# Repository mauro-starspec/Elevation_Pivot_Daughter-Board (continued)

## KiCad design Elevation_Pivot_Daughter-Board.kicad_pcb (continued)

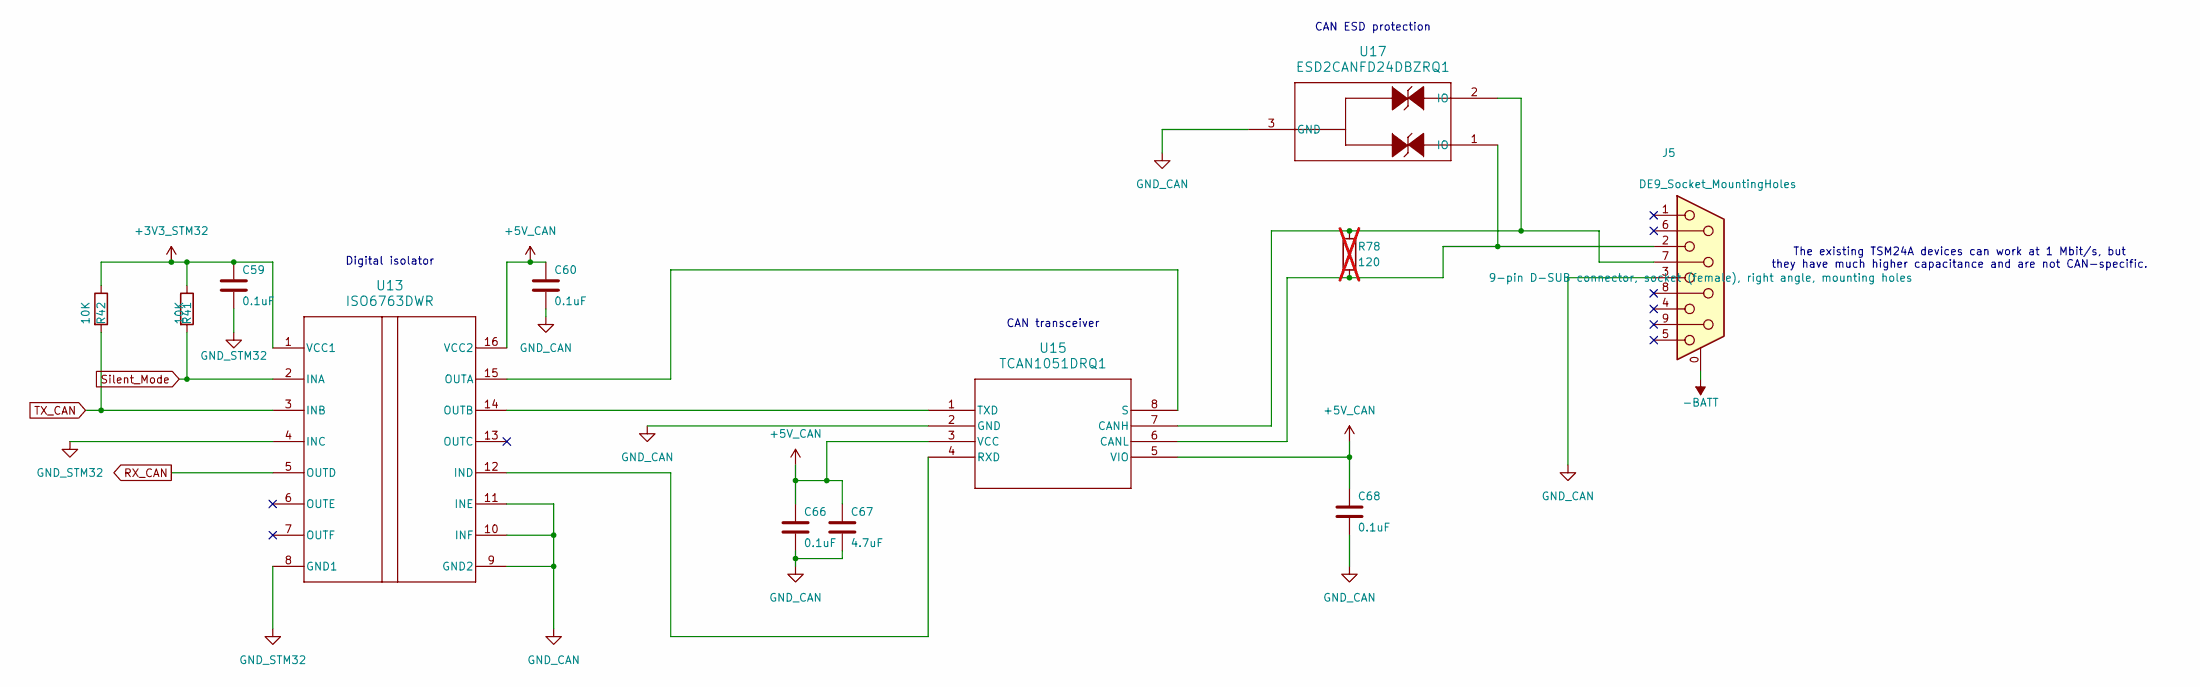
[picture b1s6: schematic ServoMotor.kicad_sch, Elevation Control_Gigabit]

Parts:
C59, C60, C66, C68: 0.1uF; C_0805_2012Metric; MANUFACTURER_PART_NUMBER CL21B104KCFNNNE; LCSC C28233
C67: 4.7uF; C_1210_3225Metric; MANUFACTURER_PART_NUMBER CL32B475KCVZNWE; LCSC C17288249
J5: DE9_Socket_MountingHoles; DSUB-9_Socket_Horizontal_P2.77x2.84mm_EdgePinOffset7.70mm_H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; MANUFACTURER_PART_NUMBER 5747844-4; LCSC C305941
R41, R42: 10K; R_0805_2012Metric; MANUFACTURER_PART_NUMBER RC0805FR-0710KL; LCSC C84376
R78: 120; R_0805_2012Metric_Pad1.20x1.40mm_HandSolder; MANUFACTURER_PART_NUMBER RC0805FR-07120RL; LCSC C114245; not fitted
U13: ISO6763DWR; MANUFACTURER_PART_NUMBER ISO6763DWR; LCSC C5216409
U15: TCAN1051DRQ1; TCAN1051HGVDRQ1; MANUFACTURER_PART_NUMBER TCAN1051DRQ1; LCSC C2671229
U17: ESD2CANFD24DBZRQ1; MANUFACTURER_PART_NUMBER ESD2CANFD24DBZRQ1; LCSC C20345392

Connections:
+3V3_STM32: C59.1, R41.1, R42.1, U13.1 (VCC1); also elsewhere on the board
+5V_CAN: C60.1, C66.1, C67.1, C68.1, U13.16 (VCC2), U15.3 (VCC), U15.5 (VIO); also elsewhere on the board
-BATT: J5.0 (PAD); also elsewhere on the board
GND_CAN: C60.2, C66.2, C67.2, C68.2, J5.3, U13.9 (GND2), U13.10 (INF), U13.11 (INE), U15.2 (GND), U17.3 (GND); also elsewhere on the board
GND_STM32: C59.2, U13.4 (INC), U13.8 (GND1); also elsewhere on the board
unnamed: U13.12 (IND), U15.4 (RXD)
unnamed: U13.15 (OUTA), U15.8 (S)
unnamed: U13.14 (OUTB), U15.1 (TXD)
unnamed: J5.7, R78.1, U15.7 (CANH), U17.2 (IO)
unnamed: J5.2, R78.2, U15.6 (CANL), U17.1 (IO)
RX_CAN: U13.5 (OUTD); also elsewhere on the board
Silent_Mode: R41.2, U13.2 (INA); also elsewhere on the board
TX_CAN: R42.2, U13.3 (INB); also elsewhere on the board

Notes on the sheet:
CAN ESD protection
Digital isolator
The existing TSM24A devices can work at 1 Mbit/s, but they have much higher capacitance and are not CAN-specific.
CAN transceiver

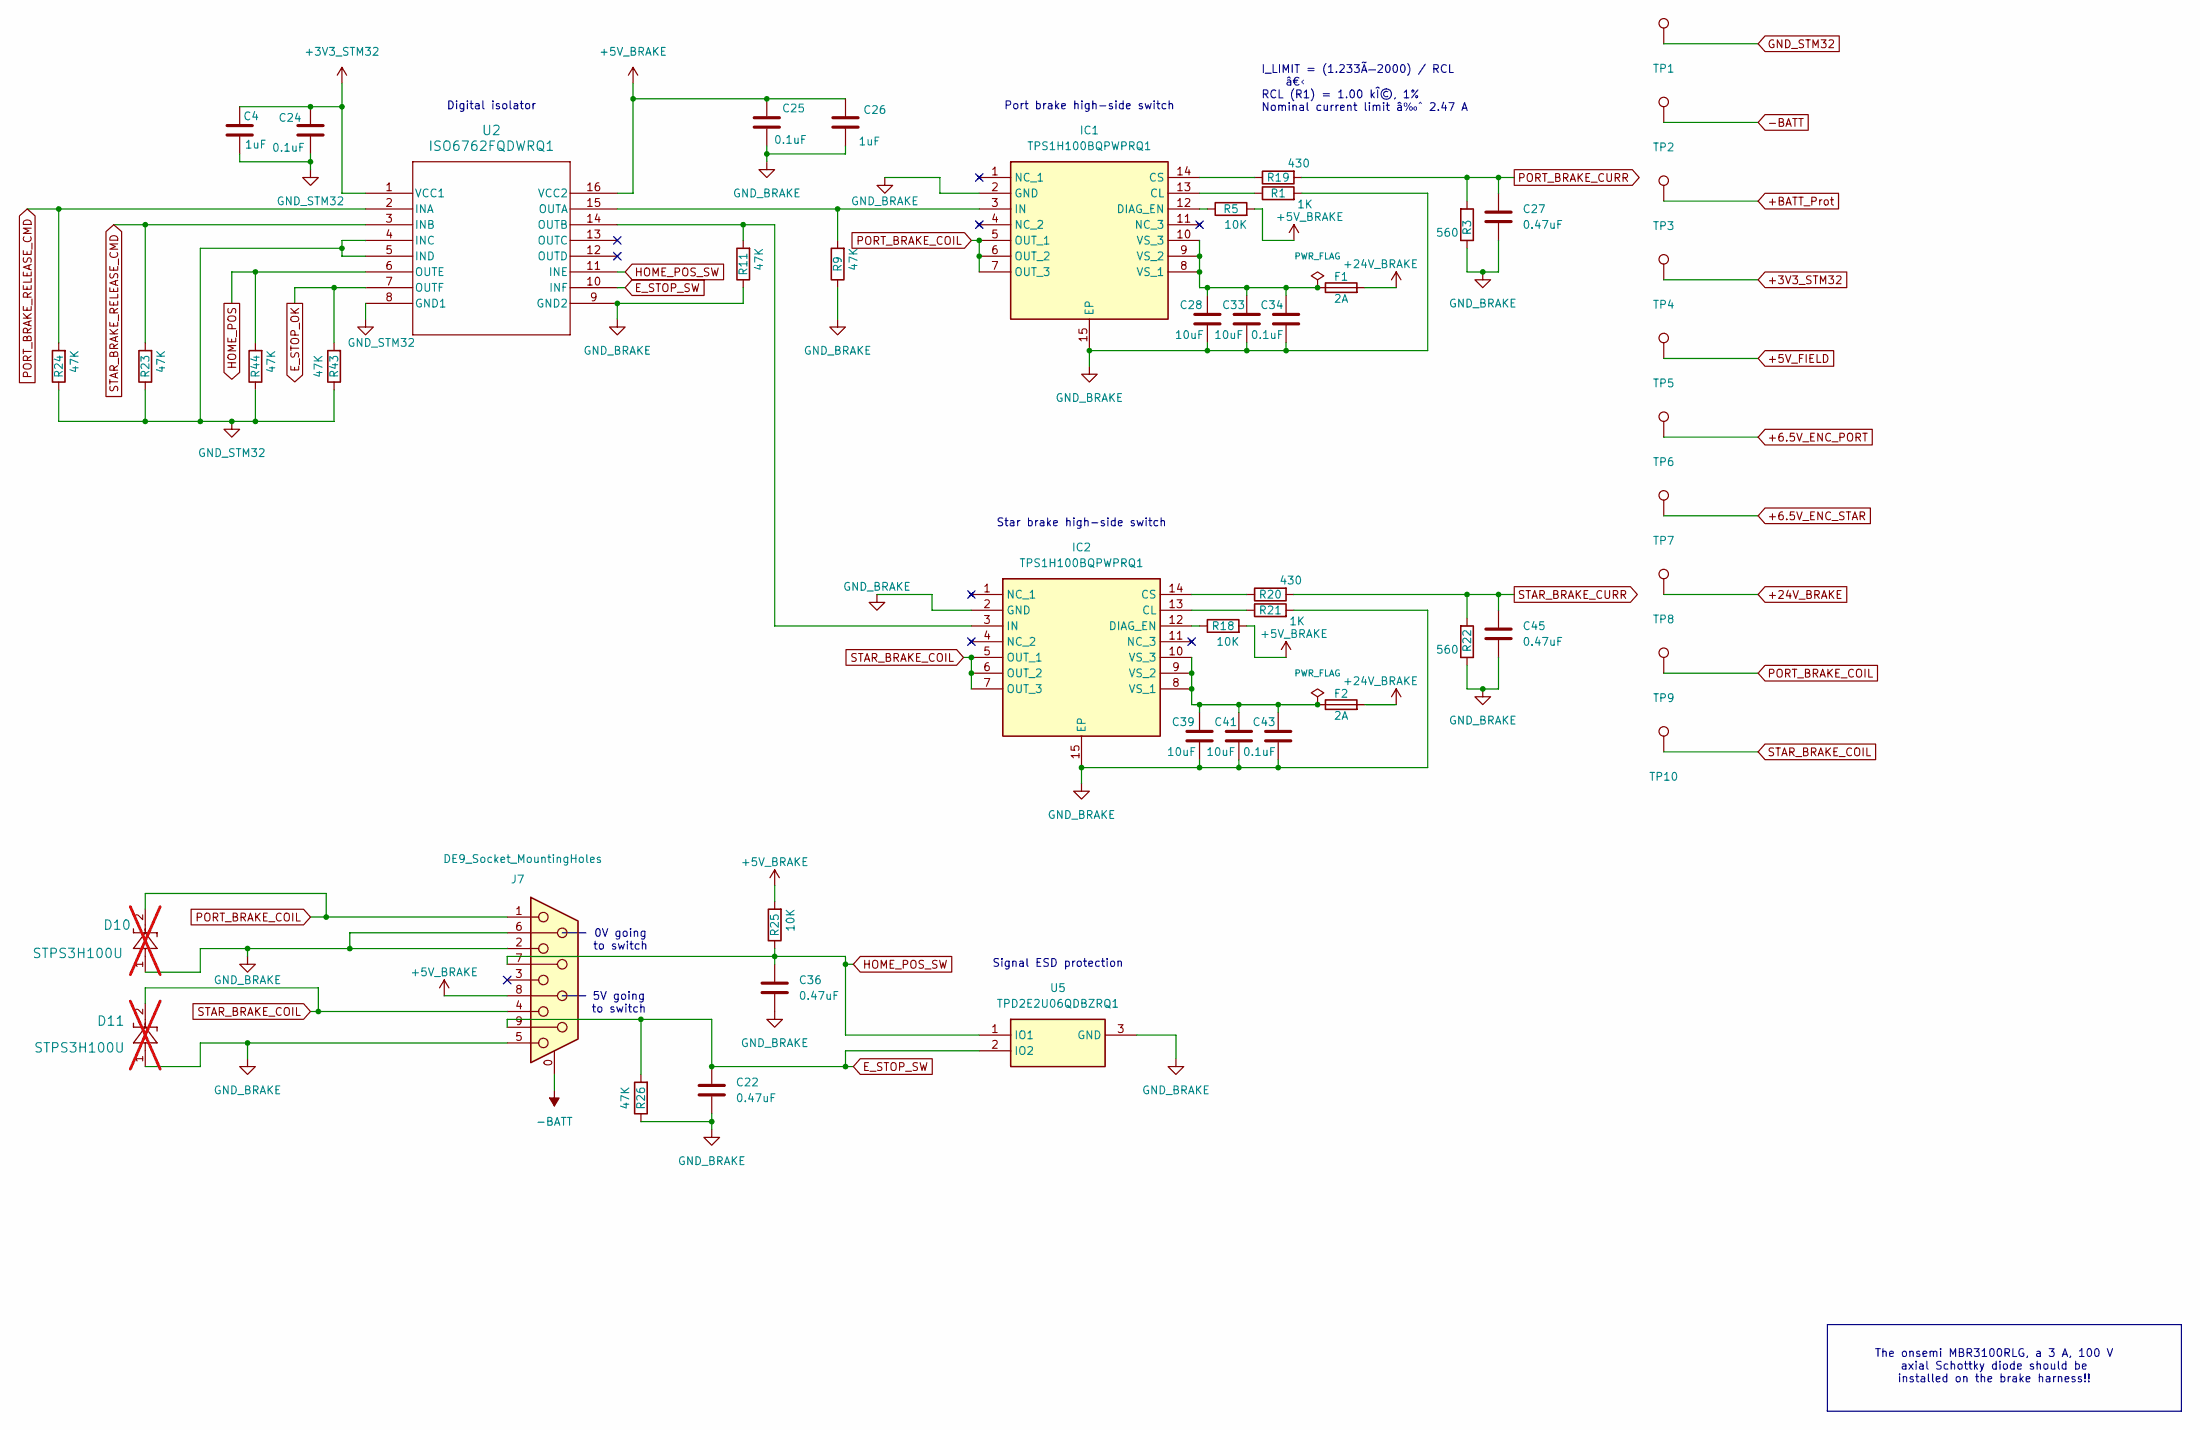
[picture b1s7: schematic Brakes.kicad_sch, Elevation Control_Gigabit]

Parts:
C4, C26: 1uF; C_1206_3216Metric; MANUFACTURER_PART_NUMBER CL31B105KCHNNNE; LCSC C13832
C22, C27, C36, C45: 0.47uF; C_0805_2012Metric; MANUFACTURER_PART_NUMBER CL21B474KBFNNNE; LCSC C13967
C24, C25, C34, C43: 0.1uF; C_0805_2012Metric; MANUFACTURER_PART_NUMBER CL21B104KCFNNNE; LCSC C28233
C28, C33, C39, C41: 10uF; C_2220_5750Metric; MANUFACTURER_PART_NUMBER FS55X106K101EHG; LCSC C153035
D10, D11: STPS3H100U; MANUFACTURER_PART_NUMBER STPS3H100U; LCSC UNVERIFIED; not fitted
F1, F2: 2A; Fuse_1206_3216Metric; MANUFACTURER_PART_NUMBER 0466002.NRHF; LCSC C3105
IC1, IC2: TPS1H100BQPWPRQ1; MANUFACTURER_PART_NUMBER TPS1H100BQPWPRQ1; LCSC C475505
J7: DE9_Socket_MountingHoles; DSUB-9_Socket_Horizontal_P2.77x2.84mm_EdgePinOffset7.70mm_H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; MANUFACTURER_PART_NUMBER 5747844-4; LCSC C305941
R1, R21: 1K; R_0805_2012Metric; MANUFACTURER_PART_NUMBER RC0805FR-071KL; LCSC C95781
R3, R22: 560; R_0805_2012Metric; MANUFACTURER_PART_NUMBER RC0805FR-07560RL; LCSC C114536
R5, R18, R25: 10K; R_0805_2012Metric; MANUFACTURER_PART_NUMBER RC0805FR-0710KL; LCSC C84376
R9, R11, R23, R24, R26, R43, R44: 47K; R_0805_2012Metric; MANUFACTURER_PART_NUMBER RC0805FR-0747KL; LCSC C126351
R19, R20: 430; R_0805_2012Metric; MANUFACTURER_PART_NUMBER RC0805FR-07430RL; LCSC C137527
TP1: GND_STM32; TestPoint_Pad_D3.0mm; MPN N/A; JLCPCB Status N/A
TP2: -BATT; TestPoint_Pad_D3.0mm; MPN N/A; JLCPCB Status N/A
TP3: +BATT_Prot; TestPoint_Pad_D3.0mm; MPN N/A; JLCPCB Status N/A
TP4: +3V3_STM32; TestPoint_Pad_D3.0mm; MPN N/A; JLCPCB Status N/A
TP5: +5V_FIELD; TestPoint_Pad_D3.0mm; MPN N/A; JLCPCB Status N/A
TP6: +6.5V_ENC_PORT; TestPoint_Pad_D3.0mm; MPN N/A; JLCPCB Status N/A
TP7: +6.5V_ENC_STAR; TestPoint_Pad_D3.0mm; MPN N/A; JLCPCB Status N/A
TP8: +24V_BRAKE; TestPoint_Pad_D3.0mm; MPN N/A; JLCPCB Status N/A
TP9: PORT_BRAKE_COIL; TestPoint_Pad_D3.0mm; MPN N/A; JLCPCB Status N/A
TP10: STAR_BRAKE_COIL; TestPoint_Pad_D3.0mm; MPN N/A; JLCPCB Status N/A
U2: ISO6762FQDWRQ1; MANUFACTURER_PART_NUMBER ISO6762FQDWRQ1; LCSC C5216383
U5: TPD2E2U06QDBZRQ1; SOT95P237X95-3N; MANUFACTURER_PART_NUMBER TPD2E2U06QDBZRQ1; LCSC C488151

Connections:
+3V3_STM32: C4.1, C24.2, TP4.1, U2.1 (VCC1); also elsewhere on the board
+5V_BRAKE: C25.2, C26.1, J7.8, R5.2, R18.2, R25.2, U2.16 (VCC2); also elsewhere on the board
+5V_FIELD: TP5.1; also elsewhere on the board
+6.5V_ENC_PORT: TP6.1; also elsewhere on the board
+6.5V_ENC_STAR: TP7.1; also elsewhere on the board
+24V_BRAKE: F1.2, F2.2, TP8.1; also elsewhere on the board
+BATT_Prot: TP3.1; also elsewhere on the board
-BATT: J7.0 (PAD), TP2.1; also elsewhere on the board
E_STOP_OK: R43.2, U2.7 (OUTF); also elsewhere on the board
E_STOP_SW: C22.1, J7.9, R26.2, U2.10 (INF), U5.2 (IO2)
GND_BRAKE: C22.2, C25.1, C26.2, C27.2, C28.2, C33.2, C34.1, C36.2, C39.2, C41.2, C43.1, C45.2, D10.1, D11.1, IC1.2 (GND), IC1.15 (EP), IC2.2 (GND), IC2.15 (EP), J7.2, J7.5, J7.6, R1.2, R3.1, R9.1, R11.1, R21.2, R22.1, R26.1, U2.9 (GND2), U5.3 (GND); also elsewhere on the board
GND_STM32: C4.2, C24.1, R23.1, R24.1, R43.1, R44.1, TP1.1, U2.4 (INC), U2.5 (IND), U2.8 (GND1); also elsewhere on the board
HOME_POS: R44.2, U2.6 (OUTE); also elsewhere on the board
HOME_POS_SW: C36.1, J7.7, R25.1, U2.11 (INE), U5.1 (IO1)
unnamed: IC1.13 (CL), R1.1
unnamed: IC1.14 (CS), R19.1
unnamed: IC1.12 (DIAG_EN), R5.1
unnamed: IC1.3 (IN), R9.2, U2.15 (OUTA)
unnamed: C28.1, C33.1, C34.2, F1.1, IC1.8 (VS_1), IC1.9 (VS_2), IC1.10 (VS_3)
unnamed: IC2.13 (CL), R21.1
unnamed: IC2.14 (CS), R20.1
unnamed: IC2.12 (DIAG_EN), R18.1
unnamed: IC2.3 (IN), R11.2, U2.14 (OUTB)
unnamed: C39.1, C41.1, C43.2, F2.1, IC2.8 (VS_1), IC2.9 (VS_2), IC2.10 (VS_3)
PORT_BRAKE_COIL: D10.2, IC1.5 (OUT_1), IC1.6 (OUT_2), IC1.7 (OUT_3), J7.1, TP9.1
PORT_BRAKE_CURR: C27.1, R3.2, R19.2; also elsewhere on the board
PORT_BRAKE_RELEASE_CMD: R24.2, U2.2 (INA); also elsewhere on the board
STAR_BRAKE_COIL: D11.2, IC2.5 (OUT_1), IC2.6 (OUT_2), IC2.7 (OUT_3), J7.4, TP10.1
STAR_BRAKE_CURR: C45.1, R20.2, R22.2; also elsewhere on the board
STAR_BRAKE_RELEASE_CMD: R23.2, U2.3 (INB); also elsewhere on the board

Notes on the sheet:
Port brake high-side switch
0V going to switch
Signal ESD protection
Digital isolator
The onsemi MBR3100RLG, a 3 A, 100 V axial Schottky diode should be installed on the brake harness!!
5V going to switch
Star brake high-side switch
I_LIMIT = (1.233Ã—2000) / RCL â€‹ RCL (R1) = 1.00 kÎ©, 1% Nominal current limit â‰ˆ 2.47 A

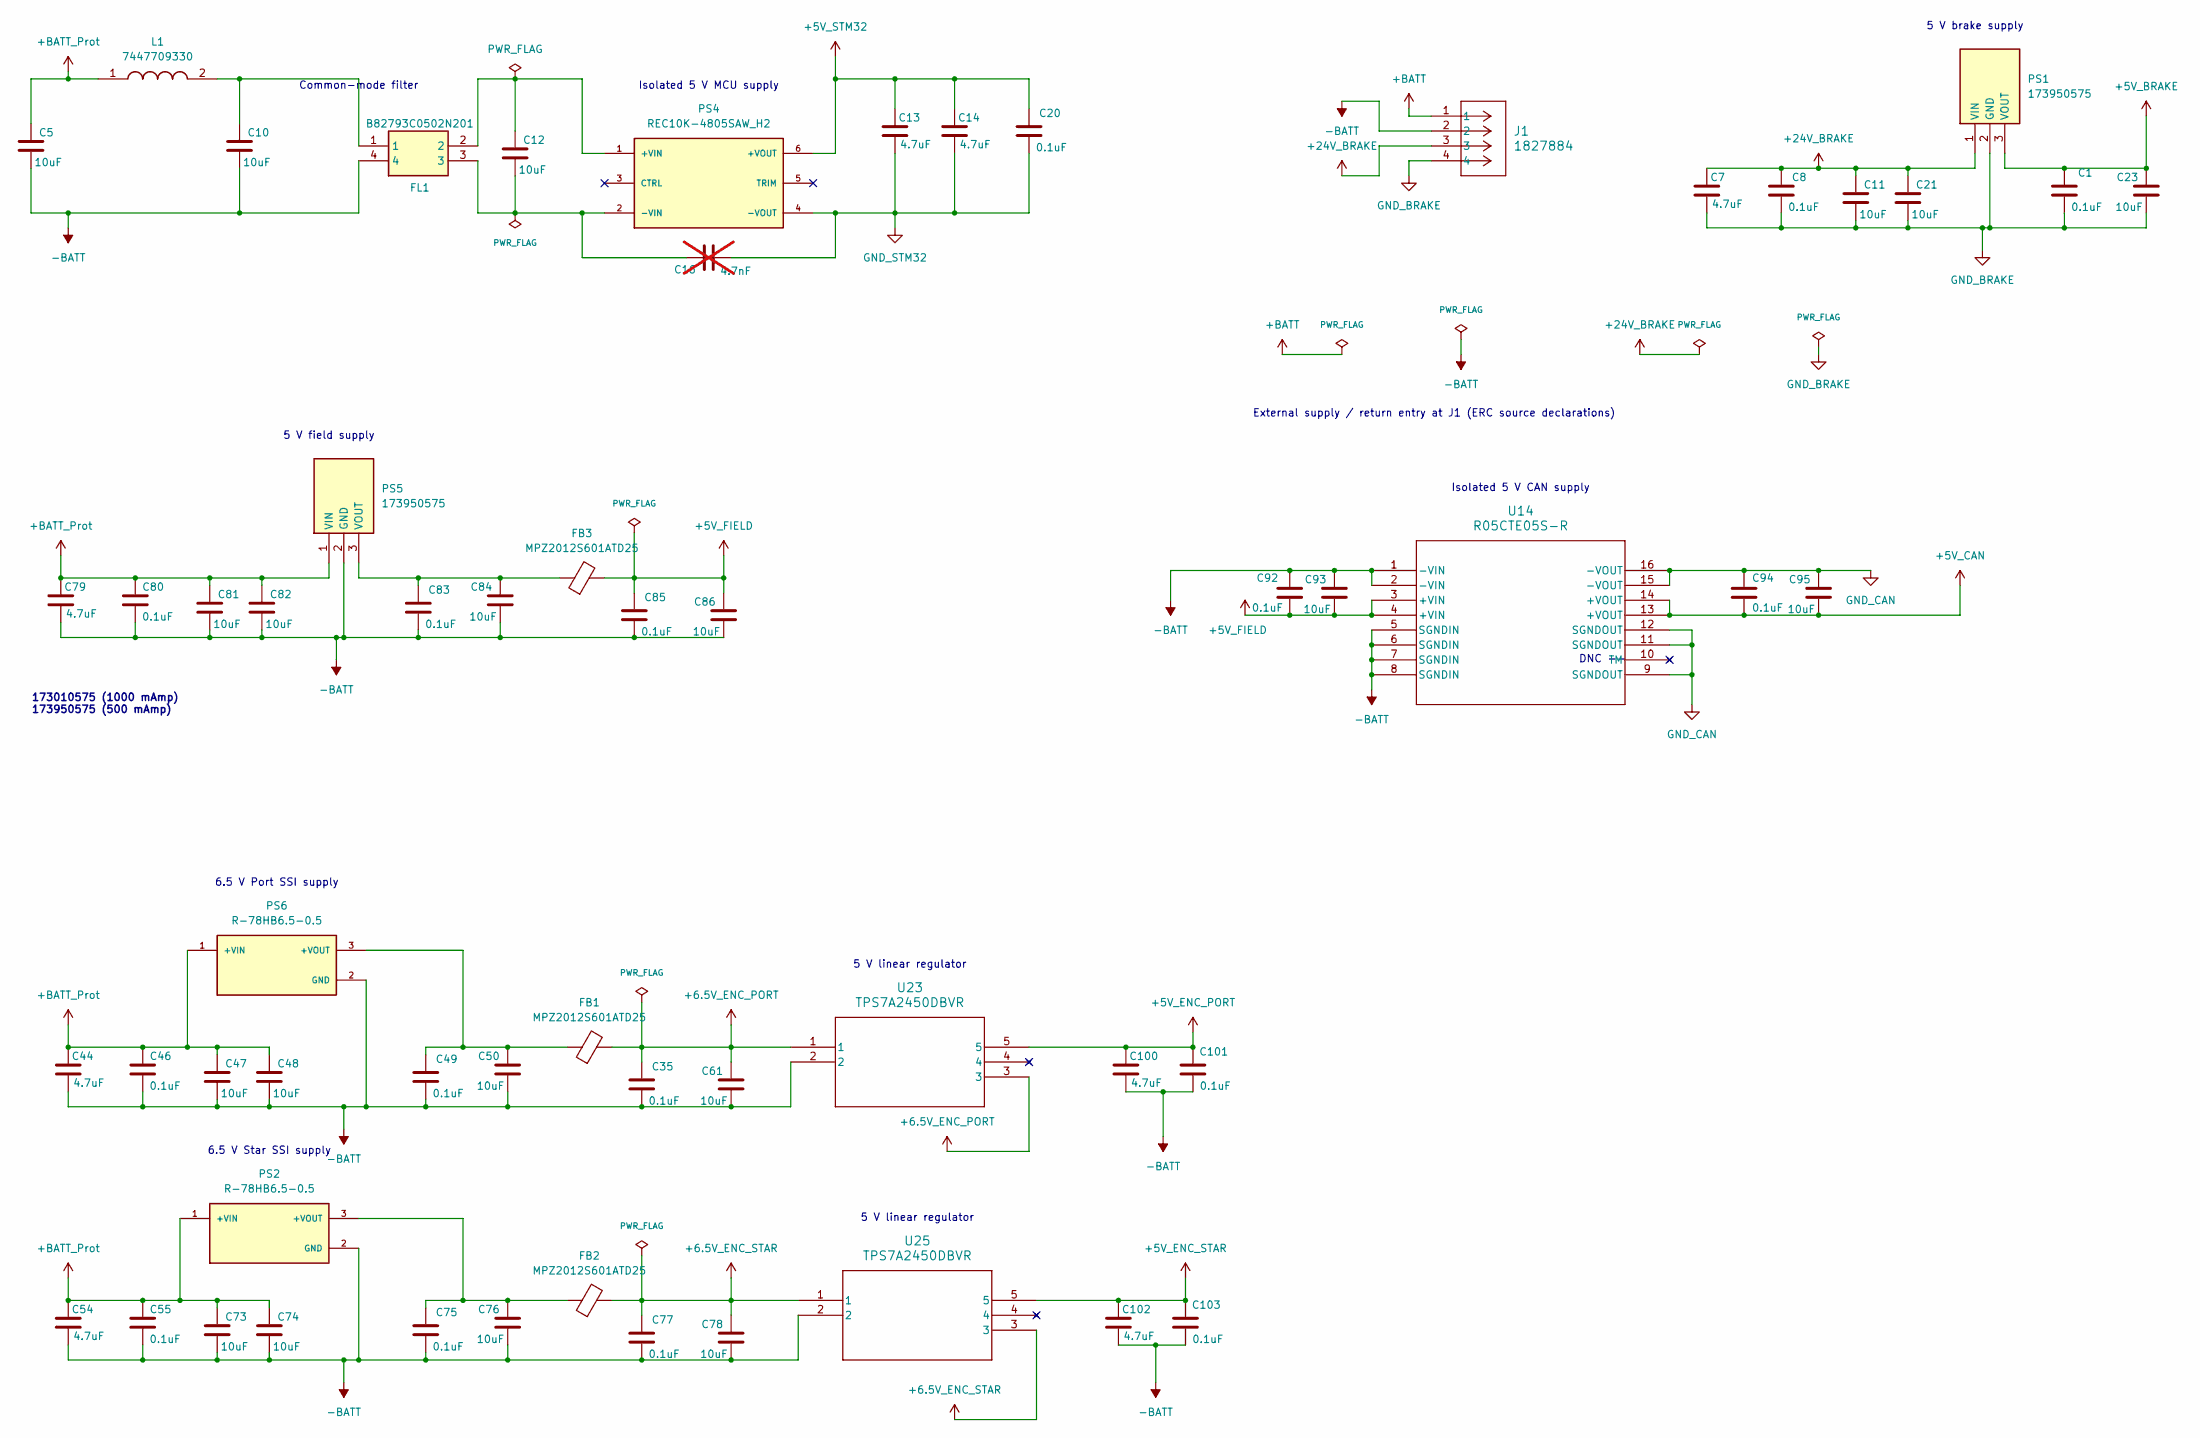
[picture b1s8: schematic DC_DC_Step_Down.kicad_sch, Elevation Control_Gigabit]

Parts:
C1, C8, C20, C35, C46, C49, C55, C75, C77, C80, C83, C85, C92, C94, C101, C103: 0.1uF; C_0805_2012Metric; MANUFACTURER_PART_NUMBER CL21B104KCFNNNE; LCSC C28233
C5, C10, C11, C12, C21, C47, C48, C73, C74, C81, C82: 10uF; C_2220_5750Metric; MANUFACTURER_PART_NUMBER FS55X106K101EHG; LCSC C153035
C7, C13, C14, C44, C54, C79, C100, C102: 4.7uF; C_1210_3225Metric; MANUFACTURER_PART_NUMBER CL32B475KCVZNWE; LCSC C17288249
C16: 4.7nF; C_2220_5750Metric; MANUFACTURER_PART_NUMBER GA355DR7GF472KW01L; LCSC C76897; not fitted
C23, C50, C61, C76, C78, C84, C86, C93, C95: 10uF; C_1210_3225Metric; MANUFACTURER_PART_NUMBER CL32B106KBJNFNE; LCSC C18739
FB1, FB2, FB3: MPZ2012S601ATD25; L_0805_2012Metric; MANUFACTURER_PART_NUMBER MPZ2012S601ATD25; LCSC C81034
FL1: B82793C0502N201; B82793C0104N201; Mouser Part Number 871-B82793C502N201
J1: 1827884; MANUFACTURER_PART_NUMBER 1827884; LCSC UNVERIFIED
L1: 7447709330; WE-PD_1260_1245_1280_121054; Mouser Part Number 710-7447709330
PS1, PS5: 173950575; Mouser Part Number 710-173950575
PS2, PS6: R-78HB6.5-0.5; R_78HB6_5_0_5; PARTREV 5; LCSC UNVERIFIED
PS4: REC10K-4805SAW_H2; PARTREV PRELIMINARY; LCSC UNVERIFIED
U14: R05CTE05S-R; R05CTE05S; MANUFACTURER_PART_NUMBER R05CTE05S-CT; LCSC C6636280
U23, U25: TPS7A2450DBVR; MANUFACTURER_PART_NUMBER TPS7A2450DBVR; LCSC C2864436

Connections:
+5V_BRAKE: C1.2, C23.1, PS1.3 (VOUT); also elsewhere on the board
+5V_CAN: C94.2, C95.2, U14.13 (+VOUT), U14.14 (+VOUT); also elsewhere on the board
+5V_ENC_PORT: C100.1, C101.2, U23.5; also elsewhere on the board
+5V_ENC_STAR: C102.1, C103.2, U25.5; also elsewhere on the board
+5V_FIELD: C85.2, C86.1, C92.1, C93.2, FB3.2, U14.3 (+VIN), U14.4 (+VIN); also elsewhere on the board
+5V_STM32: C13.1, C14.1, C20.2, PS4.6 (+VOUT); also elsewhere on the board
+6.5V_ENC_PORT: C35.2, C61.1, FB1.2, U23.1, U23.3; also elsewhere on the board
+6.5V_ENC_STAR: C77.2, C78.1, FB2.2, U25.1, U25.3; also elsewhere on the board
+24V_BRAKE: C7.1, C8.2, C11.1, C21.1, J1.3, PS1.1 (VIN); also elsewhere on the board
+BATT: J1.1; also elsewhere on the board
+BATT_Prot: C5.1, C44.1, C46.2, C47.1, C48.1, C54.1, C55.2, C73.1, C74.1, C79.1, C80.2, C81.1, C82.1, L1.1, PS2.1 (+VIN), PS5.1 (VIN), PS6.1 (+VIN); also elsewhere on the board
-BATT: C5.2, C10.2, C35.1, C44.2, C46.1, C47.2, C48.2, C49.1, C50.2, C54.2, C55.1, C61.2, C73.2, C74.2, C75.1, C76.2, C77.1, C78.2, C79.2, C80.1, C81.2, C82.2, C83.1, C84.2, C85.1, C86.2, C92.2, C93.1, C100.2, C101.1, C102.2, C103.1, FL1.4, J1.2, PS2.2 (GND), PS5.2 (GND), PS6.2 (GND), U14.1 (-VIN), U14.2 (-VIN), U14.5 (SGNDIN), U14.6 (SGNDIN), U14.7 (SGNDIN), U14.8 (SGNDIN), U23.2, U25.2; also elsewhere on the board
GND_BRAKE: C1.1, C7.2, C8.1, C11.2, C21.2, C23.2, J1.4, PS1.2 (GND); also elsewhere on the board
GND_CAN: C94.1, C95.1, U14.9 (SGNDOUT), U14.11 (SGNDOUT), U14.12 (SGNDOUT), U14.15 (-VOUT), U14.16 (-VOUT); also elsewhere on the board
GND_STM32: C13.2, C14.2, C16.2, C20.1, PS4.4 (-VOUT); also elsewhere on the board
unnamed: C10.1, FL1.1, L1.2
unnamed: C75.2, C76.1, FB2.1, PS2.3 (+VOUT)
unnamed: C12.1, FL1.2, PS4.1 (+VIN)
unnamed: C12.2, C16.1, FL1.3, PS4.2 (-VIN)
unnamed: C83.2, C84.1, FB3.1, PS5.3 (VOUT)
unnamed: C49.2, C50.1, FB1.1, PS6.3 (+VOUT)

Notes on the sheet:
5 V linear regulator
External supply / return entry at J1 (ERC source declarations)
5 V field supply
6.5 V Star SSI supply
6.5 V Port SSI supply
Isolated 5 V MCU supply
Common-mode filter
5 V brake supply
DNC --
Isolated 5 V CAN supply
173010575 (1000 mAmp) 173950575 (500 mAmp)

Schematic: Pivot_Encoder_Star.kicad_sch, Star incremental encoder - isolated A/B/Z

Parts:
C140: 10u / 100V; C_1210_3225Metric; Voltage 100 V; Tolerance 10%; MPN CGA6P1X7R2A106K250AC; JLCPCB Status No verified JLCPCB ID; source or consign
C141: 10u / 16V; C_0805_2012Metric; Voltage 16 V; Tolerance 10%; MPN CL21B106KOQNNNE; JLCPCB Status Exact catalog match; stock not verified
C142: 1u / 16V; C_0805_2012Metric; Voltage 25V; MPN C2012X7R1E105K085AB; JLCPCB Status No verified JLCPCB ID; source or consign
C145: 100n / 16V; C_0805_2012Metric; MPN CL21B104KCFNNNE; JLCPCB Status Historical ID; recheck exact part and a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
J21: DE9 FEMALE; DSUB-9_Socket_Horizontal_P2.77x2.84mm_EdgePinOffset7.70mm_H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; MPN 5747844-4; JLCPCB Library UNVERIFIED
PS11: R-78HB5.0-0.5; Converter_DCDC_RECOM_R-78HB-0.5_THT; MPN R-78HB5.0-0.5; JLCPCB Status No verified JLCPCB ID; source or consign
R130, R133, R136: 120R 1% / 0.5W; R_1206_3216Metric; Tolerance 1%; MPN ERJ-P08F1200V; JLCPCB Library UNVERIFIED
R131, R132, R134, R135, R137, R138: 560R 1%; R_0805_2012Metric; MPN RC0805FR-07560RL; JLCPCB Status Historical ID; recheck exact part and a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
U110: AM26LV32EIDR; SOIC-16_3.9x9.9mm_P1.27mm; MPN AM26LV32EIDR; JLCPCB Status Exact catalog match; stock not verified
U112, U113, U114: TPD2E2U06QDBZRQ1; SOT-23; MPN TPD2E2U06QDBZRQ1; JLCPCB Status Historical ID; recheck exact part and a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

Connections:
+3V3_MOTOR_ENC: C145.1, R131.1, R134.1, R137.1, U110.4 (G), U110.14 (4A_+), U110.16 (VCC); also elsewhere on the board
+5V_MOTOR_ENC_STAR: C141.1, C142.1, J21.1, PS11.3 (5V_OUT)
+BATT_Prot: C140.1, PS11.1 (VIN); also elsewhere on the board
-BATT: C140.2, C141.2, C142.2, C145.2, J21.2, J21.9, PS11.2 (GND), R132.2, R135.2, R138.2, U110.8 (GND), U110.12 (~G), U110.15 (4B_-), U112.3 (GND), U113.3 (GND), U114.3 (GND); also elsewhere on the board
/Pivot_Encoder_Star/A+: J21.3, R130.1, R131.2, U110.2 (1A_+), U112.1 (IO1)
/Pivot_Encoder_Star/A-: J21.4, R130.2, R132.1, U110.1 (1B_-), U112.2 (IO2)
/Pivot_Encoder_Star/B+: J21.5, R133.1, R134.2, U110.6 (2A_+), U113.1 (IO1)
/Pivot_Encoder_Star/B-: J21.6, R133.2, R135.1, U110.7 (2B_-), U113.2 (IO2)
/Pivot_Encoder_Star/Z+: J21.7, R136.1, R137.2, U110.10 (3A_+), U114.1 (IO1)
/Pivot_Encoder_Star/Z-: J21.8, R136.2, R138.1, U110.9 (3B_-), U114.2 (IO2)
PIVOT_CHASSIS: J21.0 (PAD); also elsewhere on the board
STAR_ENC_A_RX: U110.3 (1Y); also elsewhere on the board
STAR_ENC_B_RX: U110.5 (2Y); also elsewhere on the board
STAR_ENC_Z_RX: U110.11 (3Y); also elsewhere on the board

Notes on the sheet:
Quad RS-422 receiver
C145: Star receiver decoupling. Receiver and bias use shared +3V3_MOTOR_ENC from U105. Shared isolation U101 is on the Port encoder sheet.
Signal ESD protection
Z pair termination / unplug bias / ESD
Star
B pair termination / unplug bias / ESD
Bias: ~0.319 V unloaded at 3.3 V; validate with actual driver and cable. One receiver channel unused: inputs fixed; output NC. Shorted pairs are NOT detected.
5 V step-down regulator
5 V differential A/B/Z assumed; motor model and installed cable are NOT verified. Proposed board-side DE9 pinout requires a matching harness drawing. Retain existing SSI.
A pair termination / unplug bias / ESD
Star A/B/Z receiver outputs go to shared U101 on the Port encoder sheet. The six MCU outputs and their test points are on that sheet.
Shared logic power: PS10 -> U105 -> both receivers and U101. Loss of PS10 disables feedback from both motor encoders. PS11 still supplies the Star encoder itself.

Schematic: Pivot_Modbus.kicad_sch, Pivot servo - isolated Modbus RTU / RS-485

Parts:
C160, C162: 100n 16V X7R; C_0805_2012Metric; MPN CL21B104KCFNNNE; JLCPCB Status Historical ID; recheck exact part and a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
C161, C163: 1u 16V X7R; C_0805_2012Metric; Voltage 25V; MPN C2012X7R1E105K085AB; JLCPCB Status No verified JLCPCB ID; source or consign
J22: DE9 MODBUS RTU; DSUB-9_Socket_Horizontal_P2.77x2.84mm_EdgePinOffset7.70mm_H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; MPN 5747844-4; JLCPCB Library UNVERIFIED
JP160, JP161: BIAS; SolderJumper-2_P1.3mm_Bridged_RoundedPad1.0x1.5mm; MPN N/A; JLCPCB Status N/A
JP162: TERM; SolderJumper-2_P1.3mm_Bridged_RoundedPad1.0x1.5mm; MPN N/A; JLCPCB Status N/A
R160, R161, R162: 10k; R_0805_2012Metric; MPN RC0805FR-0710KL; JLCPCB Status Historical ID; recheck exact part and a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
R163, R164: 560R 1%; R_0805_2012Metric; MPN RC0805FR-07560RL; JLCPCB Status Historical ID; recheck exact part and a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
R165: 120R 1% 0.5W; R_1210_3225Metric; Voltage 200 V maximum working; Tolerance 1%; MPN RC1210FR-07120RL; JLCPCB Library UNVERIFIED
U160: ISO1410DWR; SOIC-16W_7.5x10.3mm_P1.27mm; MPN ISO1410DWR; JLCPCB Status Exact catalog match; stock not verified

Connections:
+3V3_STM32: C160.1, C161.1, R160.1, R161.1, U160.1 (VCC1); also elsewhere on the board
+5V_FIELD: C162.1, C163.1, R163.1, U160.16 (VCC2); also elsewhere on the board
-BATT: C162.2, C163.2, J22.1, JP161.1 (A), U160.9 (GND2), U160.15 (GND2); also elsewhere on the board
/Pivot_Modbus/PIVOT_RS485_D0_N: J22.9, JP162.1 (A), R164.1, U160.13 (B (-))
/Pivot_Modbus/PIVOT_RS485_D1_P: J22.5, JP160.1 (A), R165.1, U160.12 (A (+))
GND_STM32: C160.2, C161.2, R162.2, U160.2 (GND1), U160.8 (GND1); also elsewhere on the board
unnamed: JP160.2 (B), R163.2
unnamed: JP161.2 (B), R164.2
unnamed: JP162.2 (B), R165.2
PIVOT_CHASSIS: J22.0 (PAD); also elsewhere on the board
PIVOT_MODBUS_DE: R162.1, U160.4 (~RE), U160.5 (DE); also elsewhere on the board
PIVOT_MODBUS_RX: R161.2, U160.3 (R); also elsewhere on the board
PIVOT_MODBUS_TX: R160.2, U160.6 (D); also elsewhere on the board

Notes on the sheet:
PIVOT SERVO | ISOLATED MODBUS RTU, 2-WIRE RS-485
U160: RS-485 transceiver + galvanic isolation in one IC
BUS BIAS / END TERMINATION
STM32 DOMAIN
FIELD DOMAIN
J22: pivot servo communications 1 = Common (-BATT) 5 = D1 (+); 9 = D0 (-) Shell = Chassis; no power output
JP160 + JP161: closed = 560R bias pair enabled. Open BOTH if another node provides bus bias. JP162: closed = 120R termination enabled. Use termination only at the two cable ends.
USART2 / AF7: PD5 TX, PD6 RX, PD4 active-high hardware DE. DE low: listen, driver off. DE high: transmit, receiver disabled. 10k pull-down keeps the driver off during reset; TX/RX idle high. Set baud, parity, address and turnaround timing to the servo manual.
U160 A = D1 (+), U160 B = D0 (-); vendor A/B names differ. Twisted D1/D0 pair plus Common; bond shield to chassis. DE9 assignment follows Modbus Serial Line V1.02, section 3.5.1. Servo model and cable pinout remain to be confirmed.
Logic: existing +3V3_STM32 / GND_STM32. Bus: existing +5V_FIELD / -BATT. No new converter. Bus shares the battery field return; isolation protects STM32 logic. Place each 100n at its VCC pin; keep copper clear of the isolation barrier. U160 includes bus ESD protection; cable EMC and rail loading st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
Hardware provision: half-duplex RS-485, up to 500 kbit/s. Firmware Modbus client and drive register map are separate work. JP160/161/162 are copper-bridged solder links, closed by default.

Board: 4 copper layers, 245 parts (94 on the bottom side), 109 nets, no tracks yet.

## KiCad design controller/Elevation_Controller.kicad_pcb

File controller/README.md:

# P6 compact controller

Current revision: 80 x 130 mm, with the SSI and stepper interfaces now on this
board. Four DE9s, plus Ethernet, USB and SWD. Components use both faces.
Open `Elevation_Controller.kicad_pro`. Only mate with the P6 carrier.
See [current handoff](../PROJECT_HANDOFF.md) and [assembly notes](../assembly/README.md).

The following source-integration notes are historical P4/P5 context; the P6
manifest overrides their board split, connector locations and pinout.

---

# Elevation STM32H723 controller

Open `Elevation_Controller.kicad_pro` in KiCad 9. This is the upper board of the
P4 elevation/pivot stack. It uses shared Stack symbols/footprints in the parent
repository; keep that directory structure intact.

Derived from `mauro-starspec/stm32h723-controller` commit `2328ccb`. Core MCU,
Ethernet, USB-C, SWD/VCP, power and watchdog circuits are retained. Generic
expansion is replaced by the elevation interface on `07_stack_interface.kicad_sch`.

J30/J31 headers mount underneath. The carrier supplies isolated 5 V; this board
supplies shared 3.3 V logic. USB VBUS does not power it. Use an external ST-LINK
for SWD; there is no Nucleo ST-LINK processor on this board.

PCB: unrouted draft, not for manufacture. See the parent
[handoff](../PROJECT_HANDOFF.md), [integration review](../docs/CONTROLLER_STACK_P4.md)
and [assembly notes](../assembly/README.md).

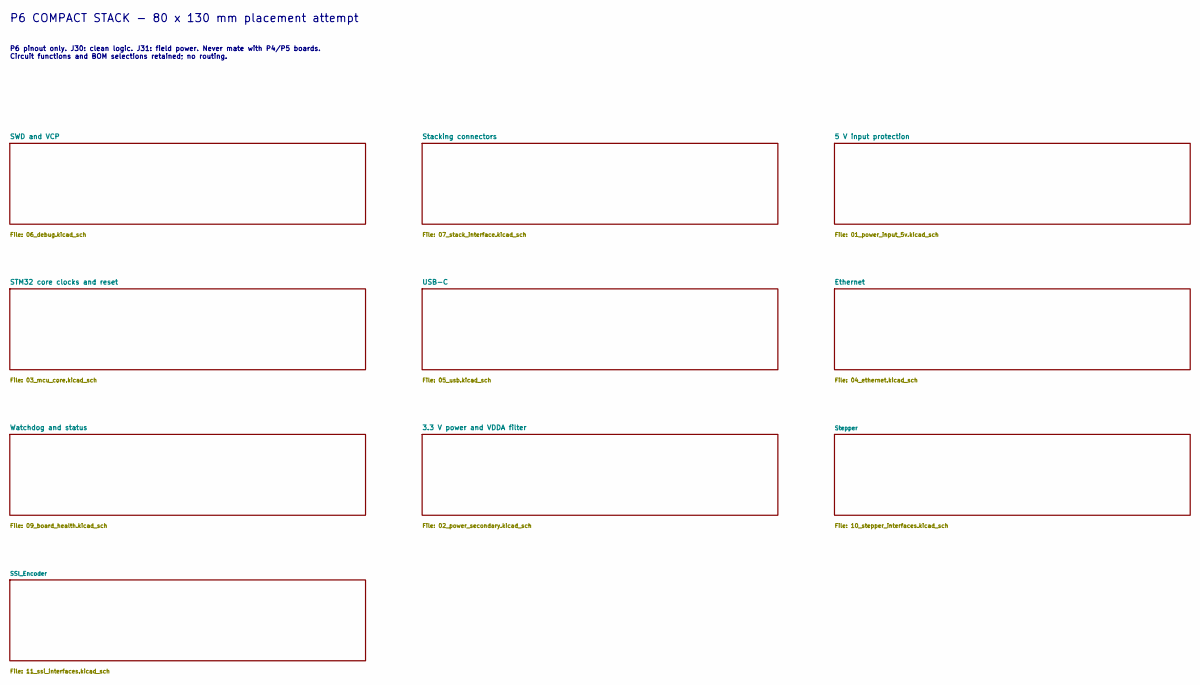
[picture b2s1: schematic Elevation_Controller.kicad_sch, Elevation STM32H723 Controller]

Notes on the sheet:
P6 COMPACT STACK - 80 x 130 mm placement attempt
P6 pinout only. J30: clean logic. J31: field power. Never mate with P4/P5 boards. Circuit functions and BOM selections retained; no routing.
